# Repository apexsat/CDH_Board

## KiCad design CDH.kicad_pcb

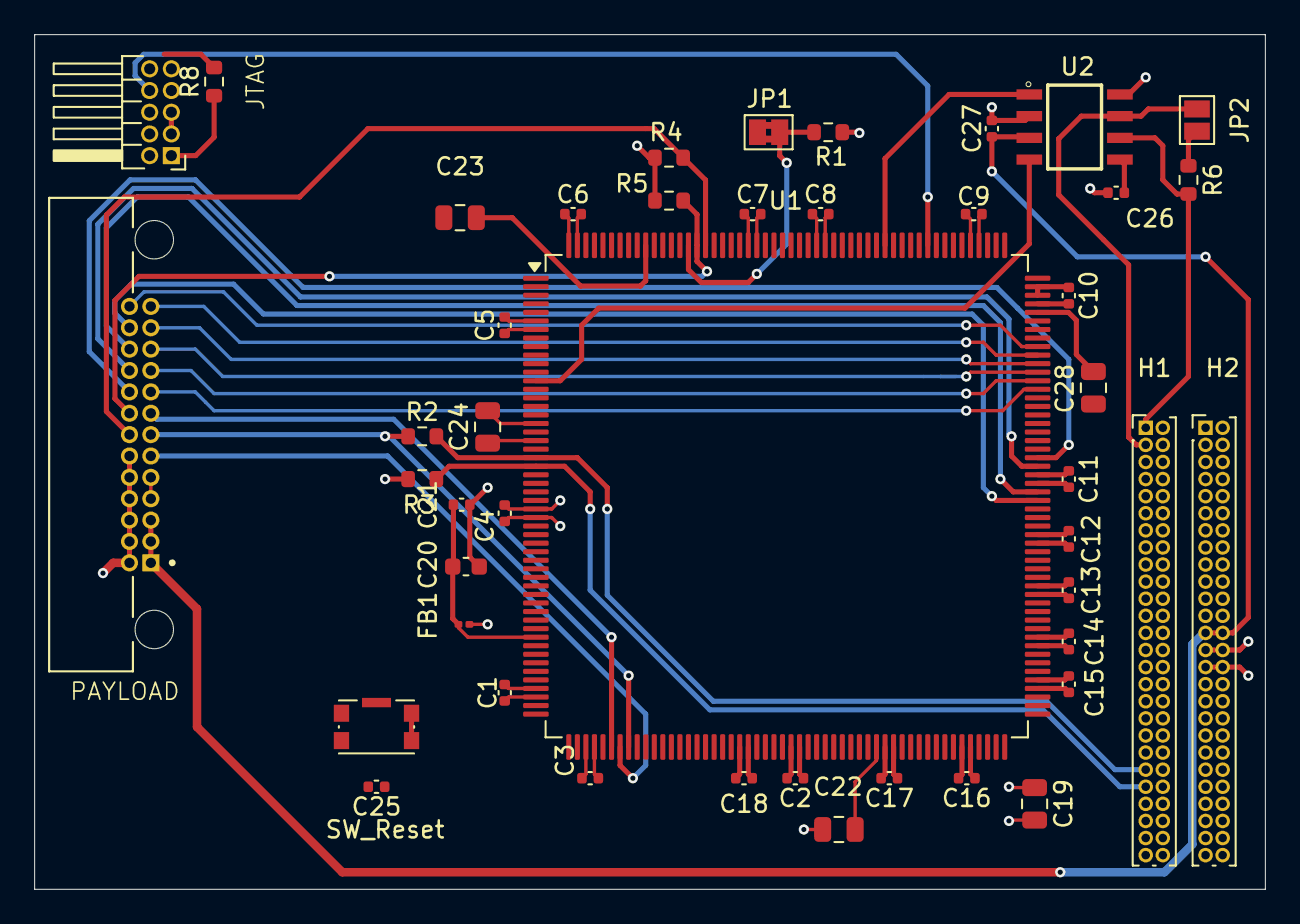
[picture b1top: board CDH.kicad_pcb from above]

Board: 4 copper layers, 72.0 x 50.0 mm, 45 parts (0 on the bottom side), 36 nets.

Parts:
C1, C2, C3, C4, C5, C6, C7, C8, C9, C10, C11, C12, C13, C14, C15, C16, C17, C18, C21, C25, C26, C27: 100n; C_0402_1005Metric
C19, C24: 4.7u; C_0805_2012Metric
C20: 1u; C_0603_1608Metric
C22, C23, C28: 2.2u; C_0805_2012Metric
FB1: FerriteBead; L_0201_0603Metric
H1, H2: Conn_02x26_Odd_Even; PinHeader_2x26_P1.00mm_Vertical
J3: G125-MH12605M4P; HARWIN_G125-MH12605M4P
J4: Conn_ARM_JTAG_SWD_10; PinHeader_2x05_P1.27mm_Horizontal
JP1: SolderJumper_2_Bridged; SolderJumper-2_P1.3mm_Bridged2Bar_Pad1.0x1.5mm
JP2: SolderJumper_2_Open; SolderJumper-2_P1.3mm_Open_Pad1.0x1.5mm
R1: 10k; R_0603_1608Metric
R2, R3, R4, R5: 4.7k; R_0603_1608Metric
R6: 120; R_0603_1608Metric
R8: 10K; R_0603_1608Metric
SW_Reset: SW_MEC_5E; SW_Push_1P1T-SH_NO_CK_KMR2xxG
U1: STM32H745BITx; LQFP-208_28x28mm_P0.5mm
U2: MCP2562FDT-H_SN; SOIC127P600X175-8N

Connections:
+5V: C27.1, H2.25, H2.26, J3.1, J3.2, J3.3, U2.3 (VDD)
/CANH_PC104: H1.3, JP2.1 (A), U2.7 (CANH)
/CANL_PC104: H1.1, R6.2, U2.6 (CANL)
/CS1: J3.9, U1.143 (PC7)
/CS2: J3.10, U1.144 (PC8)
/CS3: J3.11, U1.145 (PC9)
/CS4: J3.12, U1.146 (PA8)
/CS5: J3.13, U1.147 (PA9)
/CS6: J3.26, U1.148 (PA10)
/DEBUG_JTCK-SWCLK: J4.4 (SWCLK/TCK), U1.165 (PA14)
/DEBUG_JTDI: J4.8 (NC/TDI), U1.166 (PA15)
/DEBUG_JTDO-SWO: J4.6 (SWO/TDO), U1.189 (PB3)
/DEBUG_JTMS-SWDIO: J4.2 (SWDIO/TMS), U1.151 (PA13)
/FDCAN1_RX: U1.13 (PI9), U2.4 (RXD)
/FDCAN1_TX: U1.171 (PD1), U2.1 (TXD)
/I2C1_SCL: J3.20, R4.2, U1.192 (PB6)
/I2C1_SDA: J3.21, R5.2, U1.193 (PB7)
/I2C2_SCL: H1.43, R3.1, U1.23 (PF1)
/I2C2_SDA: H1.41, R2.2, U1.22 (PF0)
/PAY1: J3.25, U1.130 (PG2)
/PAY2: J3.24, U1.131 (PG3)
/PAY3: J3.23, U1.134 (PG4)
/PAY4: J3.22, U1.135 (PG5)
/RESET: C25.1, U1.37 (NRST)
/SPI1_MISO: J3.6, U1.59 (PA6)
/SPI1_MOSI: J3.7, U1.60 (PA7)
/SPI1_SCK: J3.8, U1.58 (PA5)
GND: C1.2, C2.2, C3.2, C4.2, C5.2, C6.2, C7.2, C8.2, C9.2, C10.2, C11.2, C12.2, C13.2, C14.2, C15.2, C16.2, C17.2, C18.2, C19.2, C20.2, C21.2, C22.1, C23.1, C24.2, C25.2, C26.1, C27.2, C28.1, H2.29, H2.30, J3.14, J3.15, J3.16, J3.17, J3.18, J3.19, J4.3 (GND), J4.5 (GND), R1.1, SW_Reset.1, SW_Reset.2, U1.6 (VSS), U1.16 (VSS), U1.18 (VSSSMPS), U1.28 (VSS), U1.42 (VSSA), U1.50 (VSS), U1.55 (VSS), U1.73 (VSS), U1.79 (VSS), U1.90 (VSS), U1.99 (VSS), U1.109 (VSS), U1.113 (VSS), U1.120 (VSS), U1.126 (VSS), U1.132 (VSS), U1.139 (VSS), U1.153 (VSS), U1.160 (VSS), U1.178 (VSS), U1.186 (VSS), U1.200 (VSS), U1.207 (VSS), U2.2 (VSS), U2.8 (STBY)
unnamed: C22.2, U1.89 (VCAP)
unnamed: C23.2, U1.199 (VCAP)
unnamed: C28.2, U1.152 (VCAP)
unnamed: J4.10 (~RESET), R8.2
unnamed: JP1.2 (B), R1.2, U1.194 (BOOT0)
unnamed: JP2.2 (B), R6.1
VDD: C1.1, C2.1, C3.1, C4.1, C5.1, C6.1, C7.1, C8.1, C9.1, C10.1, C11.1, C12.1, C13.1, C14.1, C15.1, C16.1, C17.1, C18.1, C19.1, C24.1, C26.2, FB1.2, H2.27, H2.28, J3.4, J3.5, J4.1 (VTref), JP1.1 (A), R2.1, R3.2, R4.1, R5.1, R8.1, U1.7 (VDD), U1.8 (VBAT), U1.17 (VDD), U1.20 (VDDSMPS), U1.29 (VDD), U1.49 (VDD), U1.56 (VDD), U1.74 (VDD), U1.80 (VDD), U1.91 (VDDLDO), U1.100 (VDD), U1.108 (VDD), U1.114 (VDD), U1.119 (VDD), U1.125 (VDD), U1.133 (VDD), U1.140 (VDD50_USB), U1.141 (VDD33_USB), U1.154 (VDDLDO), U1.155 (VDD), U1.161 (VDD), U1.179 (VDD), U1.187 (VDD), U1.201 (PDR_ON), U1.202 (VDDLDO), U1.208 (VDD), U2.5 (VIO)
VDDA: C20.1, C21.1, FB1.1, U1.43 (VREF+), U1.44 (VDDA)

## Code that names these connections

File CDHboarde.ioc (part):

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Mcu.Name=STM32H745BITx
Mcu.Package=LQFP208
Mcu.UserName=STM32H745BITx
PA1.GPIOParameters=GPIO_Label,PinAttribute
PA1.GPIO_Label=User Button 2
PA1.PinAttribute=Free
PA1.Signal=GPIO_Output
PA10.GPIOParameters=GPIO_Label,PinAttribute
PA10.GPIO_Label=CS6
PA10.PinAttribute=Free
PA10.Signal=GPIO_Output
PA13\ (JTMS/SWDIO).GPIOParameters=PinAttribute
PA13\ (JTMS/SWDIO).Mode=JTAG_4_pins
PA13\ (JTMS/SWDIO).PinAttribute=CortexM7
PA13\ (JTMS/SWDIO).Signal=DEBUG_JTMS-SWDIO
PA14\ (JTCK/SWCLK).GPIOParameters=PinAttribute
PA14\ (JTCK/SWCLK).Mode=JTAG_4_pins
PA14\ (JTCK/SWCLK).PinAttribute=CortexM7
PA14\ (JTCK/SWCLK).Signal=DEBUG_JTCK-SWCLK
PA15\ (JTDI).GPIOParameters=PinAttribute
PA15\ (JTDI).Mode=JTAG_4_pins
PA15\ (JTDI).PinAttribute=CortexM7
PA15\ (JTDI).Signal=DEBUG_JTDI
PA5.GPIOParameters=PinAttribute
PA5.Mode=Full_Duplex_Master
PA5.PinAttribute=CortexM7
PA5.Signal=SPI1_SCK
PA6.GPIOParameters=PinAttribute
PA6.Mode=Full_Duplex_Master
PA6.PinAttribute=CortexM7
PA6.Signal=SPI1_MISO
PA7.GPIOParameters=PinAttribute
PA7.Mode=Full_Duplex_Master
PA7.PinAttribute=CortexM7
PA7.Signal=SPI1_MOSI
PA8.GPIOParameters=GPIO_Label,PinAttribute
PA8.GPIO_Label=CS4
PA8.PinAttribute=Free
PA8.Signal=GPIO_Output
PA9.GPIOParameters=GPIO_Label,PinAttribute
PA9.GPIO_Label=CS5
PA9.PinAttribute=Free
PA9.Signal=GPIO_Output
PB12.GPIOParameters=PinAttribute
PB12.Mode=FDCAN_Activate
PB12.PinAttribute=CortexM4
PB12.Signal=FDCAN2_RX
PB13.GPIOParameters=PinAttribute
PB13.Mode=FDCAN_Activate
PB13.PinAttribute=CortexM4
PB13.Signal=FDCAN2_TX
PB3\ (JTDO/TRACESWO).GPIOParameters=PinAttribute
PB3\ (JTDO/TRACESWO).Mode=JTAG_4_pins
PB3\ (JTDO/TRACESWO).PinAttribute=CortexM7
PB3\ (JTDO/TRACESWO).Signal=DEBUG_JTDO-SWO
PB6.GPIOParameters=PinAttribute
PB6.Mode=I2C
PB6.PinAttribute=CortexM7
PB6.Signal=I2C1_SCL
PB7.GPIOParameters=PinAttribute
PB7.Mode=I2C
PB7.PinAttribute=CortexM7
PB7.Signal=I2C1_SDA
PC7.GPIOParameters=GPIO_Label,PinAttribute
PC7.GPIO_Label=CS1
PC7.PinAttribute=Free
PC7.Signal=GPIO_Output
PC8.GPIOParameters=GPIO_Label,PinAttribute
PC8.GPIO_Label=CS2
PC8.PinAttribute=Free
PC8.Signal=GPIO_Output
PC9.GPIOParameters=GPIO_Label,PinAttribute
PC9.GPIO_Label=CS3
PC9.PinAttribute=Free
PC9.Signal=GPIO_Output
PD1.GPIOParameters=PinAttribute
PD1.Mode=FDCAN_Activate
PD1.PinAttribute=CortexM7
PD1.Signal=FDCAN1_TX
PF0.GPIOParameters=PinAttribute
PF0.Mode=I2C
PF0.PinAttribute=CortexM4
PF0.Signal=I2C2_SDA
PF1.GPIOParameters=PinAttribute
PF1.Mode=I2C
PF1.PinAttribute=CortexM4
PF1.Signal=I2C2_SCL
PF10.GPIOParameters=GPIO_Label,PinAttribute
PF10.GPIO_Label=User Button 1
PF10.PinAttribute=Free
PF10.Signal=GPIO_Input
PG2.GPIOParameters=GPIO_Label,PinAttribute
PG2.GPIO_Label=PAY1
PG2.PinAttribute=Free
PG2.Signal=GPIO_Output
PG3.GPIOParameters=GPIO_Label,PinAttribute
PG3.GPIO_Label=PAY2
PG3.PinAttribute=Free
PG3.Signal=GPIO_Output
PG4.GPIOParameters=GPIO_Label,PinAttribute
PG4.GPIO_Label=PAY3
PG4.PinAttribute=Free
PG4.Signal=GPIO_Output
PG5.GPIOParameters=GPIO_Label,PinAttribute
PG5.GPIO_Label=PAY5
PG5.PinAttribute=Free
PG5.Signal=GPIO_Output
PI9.GPIOParameters=PinAttribute
PI9.Mode=FDCAN_Activate
PI9.PinAttribute=CortexM7
PI9.Signal=FDCAN1_RX
RCC.SYSCLKFreq_VALUE=64000000
board=custom

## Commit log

2025-11-24 added some labels
2025-11-25 added jtag, PAY connector, CANFD transceivers to schematic
2025-11-25 done with schematic
2025-11-29 no more ERC errors :)
2025-12-01 routing almost done
2025-12-04 changed STM32 symbol and made PCB 4 layers
